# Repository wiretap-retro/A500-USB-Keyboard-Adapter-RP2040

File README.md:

# A500 USB Keyboard Adapter RP2040
A USB keyboard adapter for the Amiga 500 based on the Pi Stamp RP2040

## Intro
This is a USB keyboard adapter I designed a board for to use in my Amiga 500 tower. It is based on the amigahid-pico firmware by borb (nine). The KiCAD files, Gerbers, and BOM are in this repository. The completed board attaches to the A500's keyboard header and provides a USB pin header for your interface device. On my build, I used a pin header to female USB Type A cable that screws into in the rear of my case on a PCI bracket.

Demo Video: https://youtu.be/7yw0AOvhLqg  (Rev 0 board with bodges/resistors. These have been corrected and implemented in Rev 1.)

## Parts
* PCB: I ordered the PCB's from JLCPCB by uploading the Gerber files, but any PCB house should be able to make these since it is a simple/small design. (PCBway, OSH Park, AllPCB, etc.)
* Pi Stamp RP2040: https://shop.pimoroni.com/products/rp2040-stamp
* All other PCB mounted components were sourced at Mouser per the BOM. Other sources for the components could be Digikey, Farnell, RS, etc. depending on what is available in your location. Chip/component shortages may impact your ability to get everything all in one place. Substitutions may need to be made.
* You will need to find a pin header to USB cable that suits your case needs. (Amazon, Ebay, Aliexpress, etc.)

## Building the Adapter
* Solder the smallest SMD components first. (resistors, capacitors, logic level shifter, MicroUSB connector)
* Solder the right angle pin connectors. (USB header, both LED headers)
* Solder the through-hole LED resistors.
* Solder the Pi Stamp RP2040 into place. You can solder directly onto the board, or optionally use the male and female headers to socket mount it. I recommend using the male and female pin headers so you can easily pull the RP2040 out if you need to use it again in the future on another project.
* Solder the vertical USB_BOOT header into place. The J5 and J6 headers are optional and untested on this design. J5 is for a small OLED screen, and J6 is for debugging.
* Solder the A500 keyboard connector female headers onto the rear of the PCB. There are two, since some revisions of A500's may have the clock and data pins swapped.
* I recommend checking all solder joints under magnification to ensure everything is connected with no shorts.

## Flashing the Firmware
First off, a huge thank you to Nine for developing the amigahid-pico, as this design uses its firmware. Firmware is located at: https://github.com/borb/amigahid-pico/
1. Build the firmware per the instructions at https://github.com/borb/amigahid-pico/blob/main/doc/installation.md
2. Place a jumper on the USB_BOOT pin.
3. Plug a MicroUSB cable to the PCB's MicroUSB port and plug the other end into the PC you just compiled the firmware on. It will then show up as a mass storage device.
4. Remove the jumper from the USB_BOOT pin.
5. Copy the amigahid-pico.uf2 file from the "build/src/" directory you compiled to the RP2040's mounted USB storage volume. It will then disconnect/reset.
6. Disconnect the USB cable from the PC and keyboard adapter PCB.

## Installation into the Amiga
1. Gain access to your Amiga 500 motherboard.
2. Disconnect the keyboard if it is still connected.
3. Plug the PCB into the A500's keyboard header either the Type A or Type B socket. For reference my Amiga 500 Rev 6A needed Type A.
4. Plug your USB cable into the pin header. Pay close attention to the orientation of the leads.
5. Plug the keyboard or wireless keyboard adapter into the other end of the USB cable.
6. Boot the Amiga and test it out!

## Optional Stuff
* If using a tower case, you can plug in the Power LED and HDD LED to the pin headers on the PCB to show the status indications.
* USB HID mouse support is included in Nine's firmware, but none of the mice I used would work with it. I use a DB9 connected OpenLaserMouse anyway, but maybe you'll have better luck testing various mice to see if one works. I know the firmware is still an in-progress project, or maybe I didn't do something right when I compiled the firmware. 
* Amiga keys are currently mapped to right and left windows keys. Before compiling the firmware, you can modify those keys if necessary at your own discretion.
* Reset is initiated by Left Ctrl + Left Win + Right Win (CTRL + AMIGA + AMIGA)

## Miscellaneous
This board is provided as-is and open source. It does not provide firmware and relies on a different project as linked above. I have personally built and tested this on my Amiga 500 Rev 6A with a custom mechanical keyboard utilizing QMK/VIA firmware.
If you plan to sell this board, firmware is per the license at: https://github.com/borb/amigahid-pico/

## Revisions
* Rev 2 - Current rev, corrected floating ground on logic conversion.
* Rev 1 - Corrected resistor pullup/pulldown. Depreciated.
* Rev 0 - Depreciated

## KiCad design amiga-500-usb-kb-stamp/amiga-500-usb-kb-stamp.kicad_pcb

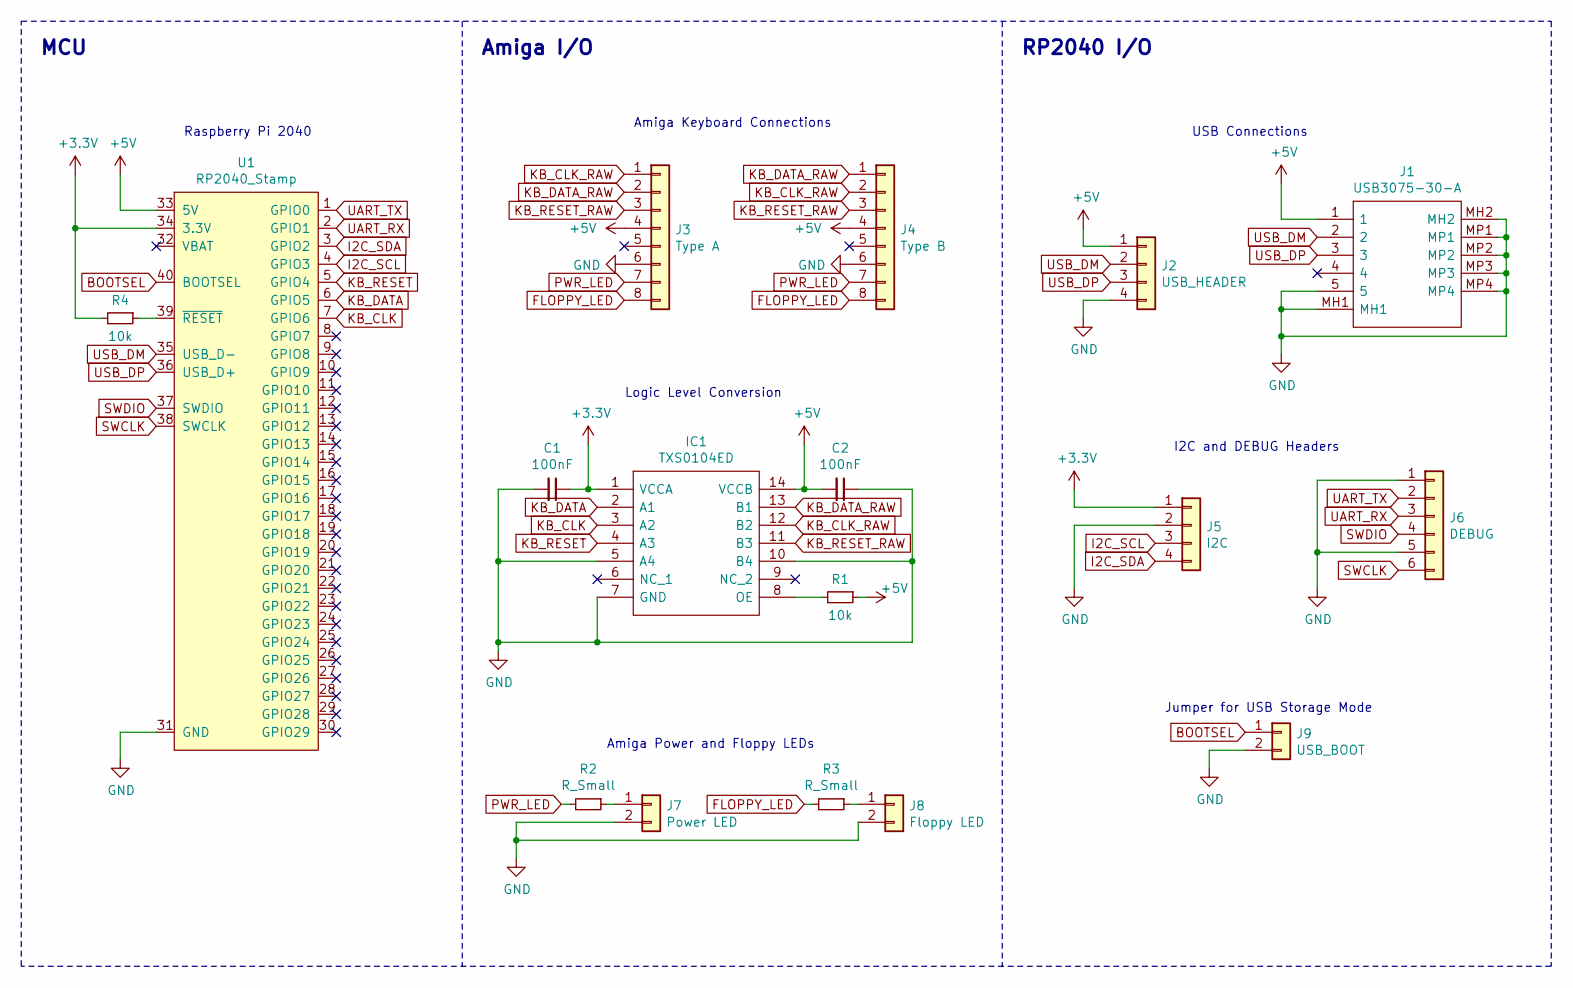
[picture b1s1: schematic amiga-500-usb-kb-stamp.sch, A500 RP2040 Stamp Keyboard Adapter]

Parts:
C1, C2: 100nF; C_0805_2012Metric_Pad1.15x1.40mm_HandSolder
IC1: TXS0104ED; SOIC127P600X175-14N; Mouser Part Number 595-TXS0104ED
J1: USB3075-30-A; USB307530A; Mouser Part Number 640-USB3075-30-A
J2: USB_HEADER; PinHeader_1x04_P2.54mm_Horizontal
J3: Type A; PinSocket_1x08_P2.54mm_Vertical
J4: Type B; PinSocket_1x08_P2.54mm_Vertical
J5: I2C; PinHeader_1x04_P2.54mm_Vertical
J6: DEBUG; PinHeader_1x06_P2.54mm_Vertical
J7: Power LED; PinHeader_1x02_P2.54mm_Horizontal
J8: Floppy LED; PinHeader_1x02_P2.54mm_Horizontal
J9: USB_BOOT; PinHeader_1x02_P2.54mm_Vertical
R1, R4: 10k; R_0805_2012Metric_Pad1.15x1.40mm_HandSolder
R2, R3: R_Small; R_Axial_DIN0207_L6.3mm_D2.5mm_P7.62mm_Horizontal
U1: RP2040_Stamp; RP2040_Stamp_THT

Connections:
+3V3: C1.1, IC1.1 (VCCA), J5.1, R4.2, U1.34 (3.3V)
+5V: C2.2, IC1.14 (VCCB), J1.1, J2.1, J3.4, J4.4, R1.1, U1.33 (5V)
BOOTSEL: J9.1, U1.40 (BOOTSEL)
FLOPPY_LED: J3.8, J4.8, R3.2
GND: C1.2, C2.1, IC1.5 (A4), IC1.7 (GND), IC1.10 (B4), J1.5, J1.MH1, J1.MH2, J1.MP1, J1.MP2, J1.MP3, J1.MP4, J2.4, J3.6, J4.6, J5.2, J6.1, J6.5, J7.2, J8.2, J9.2, U1.31 (GND)
I2C_SCL: J5.3, U1.4 (GPIO3)
I2C_SDA: J5.4, U1.3 (GPIO2)
KB_CLK: IC1.3 (A2), U1.7 (GPIO6)
KB_CLK_RAW: IC1.12 (B2), J3.1, J4.2
KB_DATA: IC1.2 (A1), U1.6 (GPIO5)
KB_DATA_RAW: IC1.13 (B1), J3.2, J4.1
KB_RESET: IC1.4 (A3), U1.5 (GPIO4)
KB_RESET_RAW: IC1.11 (B3), J3.3, J4.3
unnamed: IC1.8 (OE), R1.2
unnamed: J7.1, R2.1
unnamed: J8.1, R3.1
unnamed: R4.1, U1.39 (~RESET)
PWR_LED: J3.7, J4.7, R2.2
SWCLK: J6.6, U1.38 (SWCLK)
SWDIO: J6.4, U1.37 (SWDIO)
UART_RX: J6.3, U1.2 (GPIO1)
UART_TX: J6.2, U1.1 (GPIO0)
USB_DM: J1.2, J2.2, U1.35 (USB_D-)
USB_DP: J1.3, J2.3, U1.36 (USB_D+)

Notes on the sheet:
Jumper for USB Storage Mode
Amiga Power and Floppy LEDs
I2C and DEBUG Headers
USB Connections
Logic Level Conversion
Amiga Keyboard Connections
Raspberry Pi 2040
MCU
Amiga I/O
RP2040 I/O

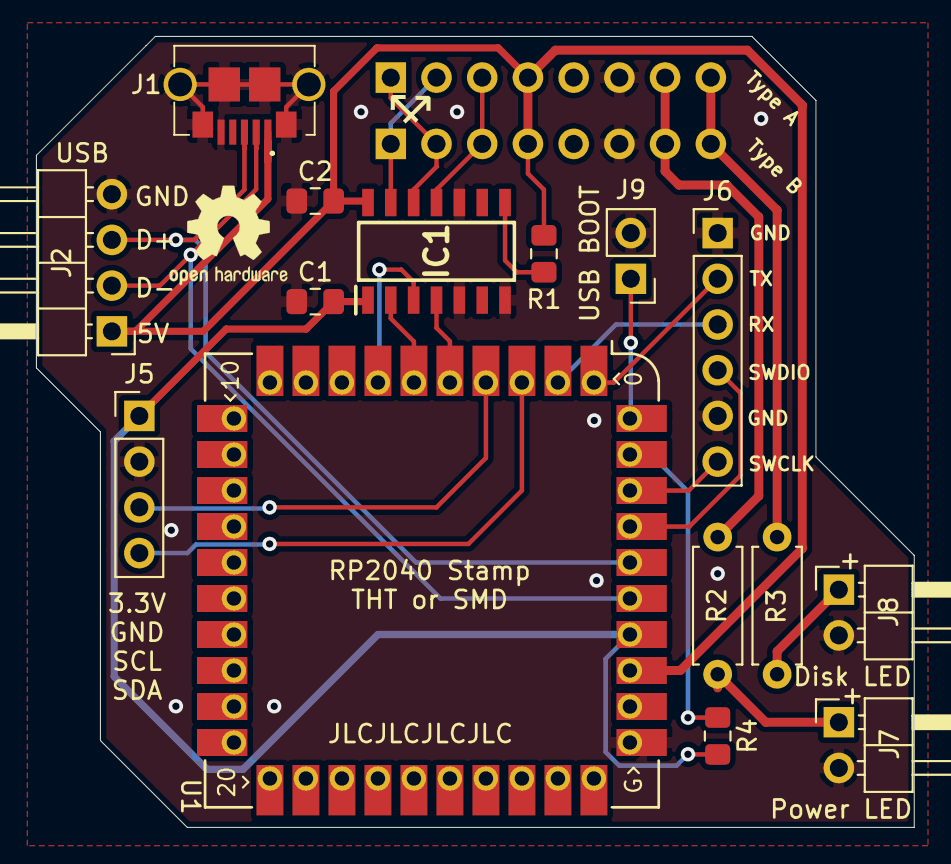
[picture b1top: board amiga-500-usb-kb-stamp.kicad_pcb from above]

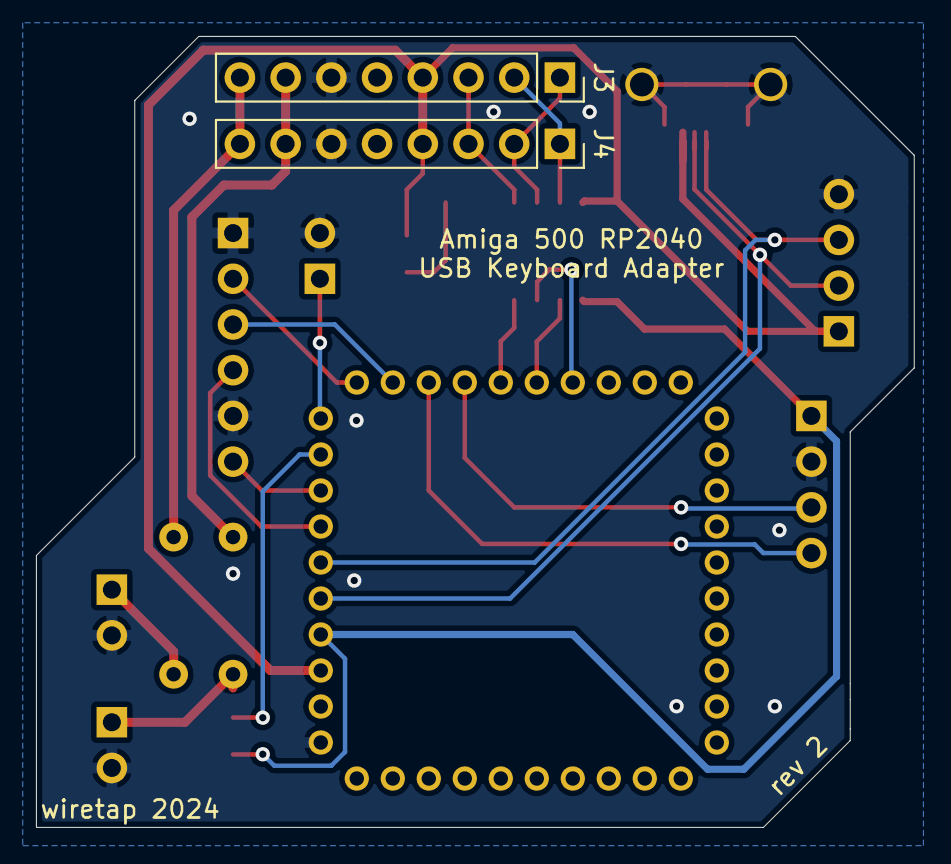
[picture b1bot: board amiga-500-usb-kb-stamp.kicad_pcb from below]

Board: 2 copper layers, 48.8 x 43.9 mm, 17 parts (2 on the bottom side), 24 nets.

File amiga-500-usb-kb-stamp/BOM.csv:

Reference, Quantity, Value, Footprint, Description, Manufacturer_Name, Manufacturer_Part_Number, Mouser Part Number
C1 C2 ,2,100nF,Capacitor_SMD:C_0805_2012Metric_Pad1.15x1.40mm_HandSolder,,,,
IC1 ,1,TXS0104ED,SOIC127P600X175-14N,"TXS0104ED, Voltage Level Translator, Open Drain 1.65 to 3.6, 2.3 to 5.5V 14-Pin SOIC",Texas Instruments,TXS0104ED,595-TXS0104ED
J1 ,1,USB3075-30-A,USB307530A,"GCT (GLOBAL CONNECTOR TECHNOLOGY) - USB3075-30-A - USB Connector, Micro USB Type B, USB 2.0, Receptacle, 5 Ways, Surface Mount, Right Angle",GCT (GLOBAL CONNECTOR TECHNOLOGY),USB3075-30-A,640-USB3075-30-A
J2 ,1,USB_HEADER,Connector_PinHeader_2.54mm:PinHeader_1x04_P2.54mm_Horizontal,,,,
J3 ,1,Type A,Connector_PinSocket_2.54mm:PinSocket_1x08_P2.54mm_Vertical,,,,
J4 ,1,Type B,Connector_PinSocket_2.54mm:PinSocket_1x08_P2.54mm_Vertical,,,,
J5 ,1,I2C,Connector_PinHeader_2.54mm:PinHeader_1x04_P2.54mm_Vertical,,,,
J6 ,1,DEBUG,Connector_PinHeader_2.54mm:PinHeader_1x06_P2.54mm_Vertical,,,,
J7 ,1,Power LED,Connector_PinHeader_2.54mm:PinHeader_1x02_P2.54mm_Horizontal,,,,
J8 ,1,Floppy LED,Connector_PinHeader_2.54mm:PinHeader_1x02_P2.54mm_Horizontal,,,,
J9 ,1,USB_BOOT,Connector_PinHeader_2.54mm:PinHeader_1x02_P2.54mm_Vertical,,,,
R1 R4,1,10k,Resistor_SMD:R_0805_2012Metric_Pad1.15x1.40mm_HandSolder,,,,
R2 R3 ,2,TBD,Resistor_THT:R_Axial_DIN0207_L6.3mm_D2.5mm_P7.62mm_Horizontal,Match to your LED requirements,,,
U1 ,1,RP2040_Stamp,SamacSys_Parts:RP2040_Stamp_THT,,,,

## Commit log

2022-09-08 Added initial files.
    Rev 1 upload.
2022-09-08 Created README.md
    First rev of the README.md file
